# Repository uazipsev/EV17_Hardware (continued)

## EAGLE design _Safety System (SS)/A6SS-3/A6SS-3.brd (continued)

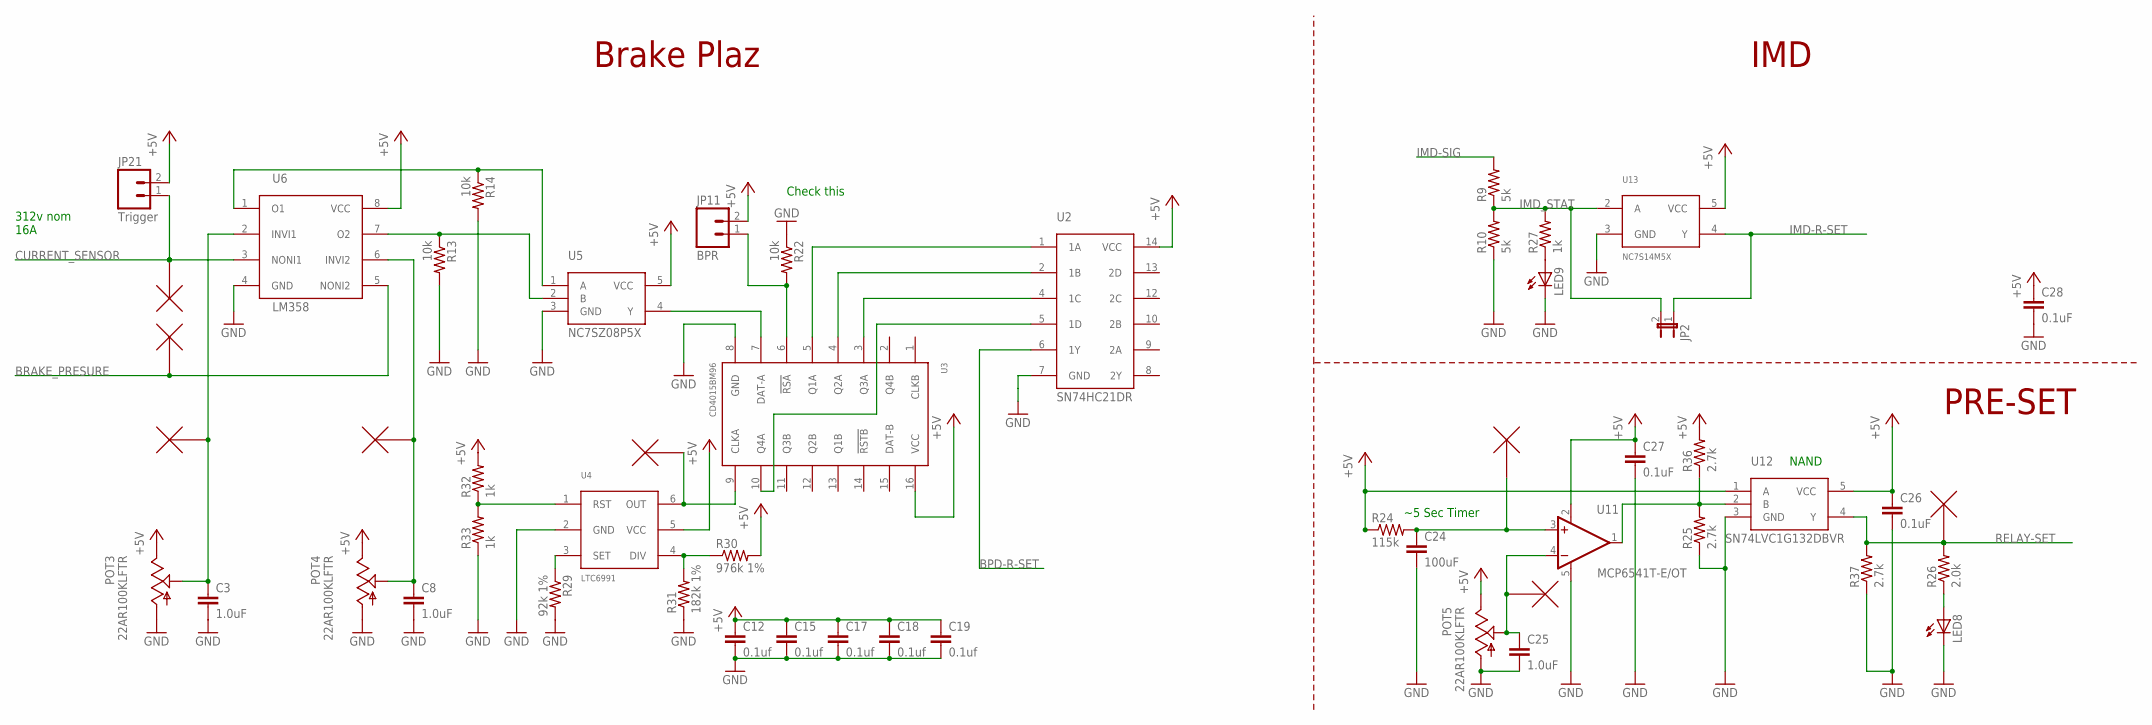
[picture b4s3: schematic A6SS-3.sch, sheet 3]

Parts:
BPR: TESTPOINT; R0603
C3, C8, C25: 1.0uF; 0805
C12, C15, C17, C18: 0.1uf; 0603-CAP
C19: 0.1uf; 0805
C24: 100uF; 1206
C26, C27: 0.1uF; 0603-CAP
C28: 0.1uF; 0805
CLK: TESTPOINT; R0603
CS: TESTPOINT; R0603
CST: TESTPOINT; R0603
JP2: JUMPER-2SMD-NO; SJ_2S-NO
JP11: BPR; MOLEX-1X2_LOCK
JP21: Trigger; MOLEX-1X2_LOCK
LED8, LED9: LEDCHIPLED_0603; CHIPLED_0603
PCG: TESTPOINT; R0603
POT3, POT4, POT5: 22AR100KLFTR
R9, R10: 5k; 0603-RES
R13, R14, R22: 10k; 0603-RES
R24: 115k; 1206
R25, R36, R37: 2.7k; 0603-RES
R26: 2.0k; 0603-RES
R27, R32, R33: 1k; 0603-RES
R29: 92k 1%; 0603-RES
R30: 976k 1%; 0603-RES
R31: 182k 1%; 0603-RES
RST: TESTPOINT; R0603
U2: SN74HC21DR; SO14
U3: CD4015BM96; SO-16
U4: LTC6991; TSOT-23-6
U5: NC7SZ08P5X; SOT23-5
U6: LM358; TSSOP-8
U11: MCP6541T-E/OT; SOT23-5
U12: SN74LVC1G132DBVR; SOT23-5
U13: NC7S14M5X; SOT23-5
U$2, U$3: TESTPOINT; R0603

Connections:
+5V: C12.1, C15.1, C17.1, C18.1, C19.1, C26.1, C27.1, C28.1, JP11.2, JP21.2, POT3.1 (CCW), POT4.1 (CCW), POT5.1 (CCW), R24.1, R30.2, R32.2, R36.2, U2.14 (VCC), U3.16 (VCC), U4.5 (VCC), U5.5 (VCC), U6.8 (VCC), U11.2 (V-), U12.1 (A), U12.5 (VCC), U13.5 (VCC); also elsewhere on the board
BPD-R-SET: U2.6 (1Y); also elsewhere on the board
BRAKE_PRESURE: BPR.1, BPR.2, U6.5 (NONI2); also elsewhere on the board
CURRENT_SENSOR: CS.1, CS.2, JP21.1, U6.3 (NONI1); also elsewhere on the board
GND: C3.2, C8.2, C12.2, C15.2, C17.2, C18.2, C19.2, C24.2, C25.2, C26.2, C27.2, C28.2, LED8.C, LED9.C, POT3.3 (CW), POT4.3 (CW), POT5.3 (CW), R10.1, R13.2, R14.2, R22.1, R25.1, R29.2, R31.1, R33.1, R37.1, U2.7 (GND), U3.8 (GND), U4.2 (GND), U5.3 (GND), U6.4 (GND), U11.5 (V+), U12.3 (GND), U13.3 (GND); also elsewhere on the board
IMD-R-SET: JP2.1, U13.4 (Y); also elsewhere on the board
IMD-SIG: R9.2; also elsewhere on the board
IMD_STAT: JP2.2, R9.1, R10.2, R27.2, U13.2 (A); also elsewhere on the board
unnamed: C25.1, POT5.2 (W), RST.1, RST.2, U11.4 (-IN)
unnamed: U2.5 (1D), U3.10 (Q4A)
unnamed: R30.1, R31.2, U4.4 (DIV)
unnamed: U3.7 (DAT-A), U5.4 (Y)
unnamed: JP11.1, R22.2, U3.6 (!RSA)
unnamed: C24.1, R24.2, U11.3 (+IN), U$2.1, U$2.2
unnamed: U2.1 (1A), U3.5 (Q1A)
unnamed: U2.2 (1B), U3.4 (Q2A)
unnamed: U2.4 (1C), U3.3 (Q3A)
unnamed: R29.1, U4.3 (SET)
unnamed: CLK.1, CLK.2, U3.9 (CLKA), U4.6 (OUT)
unnamed: C8.1, PCG.1, PCG.2, POT4.2 (W), U6.6 (INVI2)
unnamed: R25.2, R36.1, U11.1 (OUT), U12.2 (B)
unnamed: R32.1, R33.2, U4.1 (RST)
unnamed: C3.1, CST.1, CST.2, POT3.2 (W), U6.2 (INVI1)
unnamed: R14.1, U5.1 (A), U6.1 (O1)
unnamed: LED8.A, R26.1
unnamed: R13.1, U5.2 (B), U6.7 (O2)
unnamed: LED9.A, R27.1
RELAY-SET: R26.2, R37.2, U12.4 (Y), U$3.1, U$3.2; also elsewhere on the board

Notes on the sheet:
312v nom 16A
Check this
Brake Plaz
IMD
PRE-SET
~5 Sec Timer
NAND

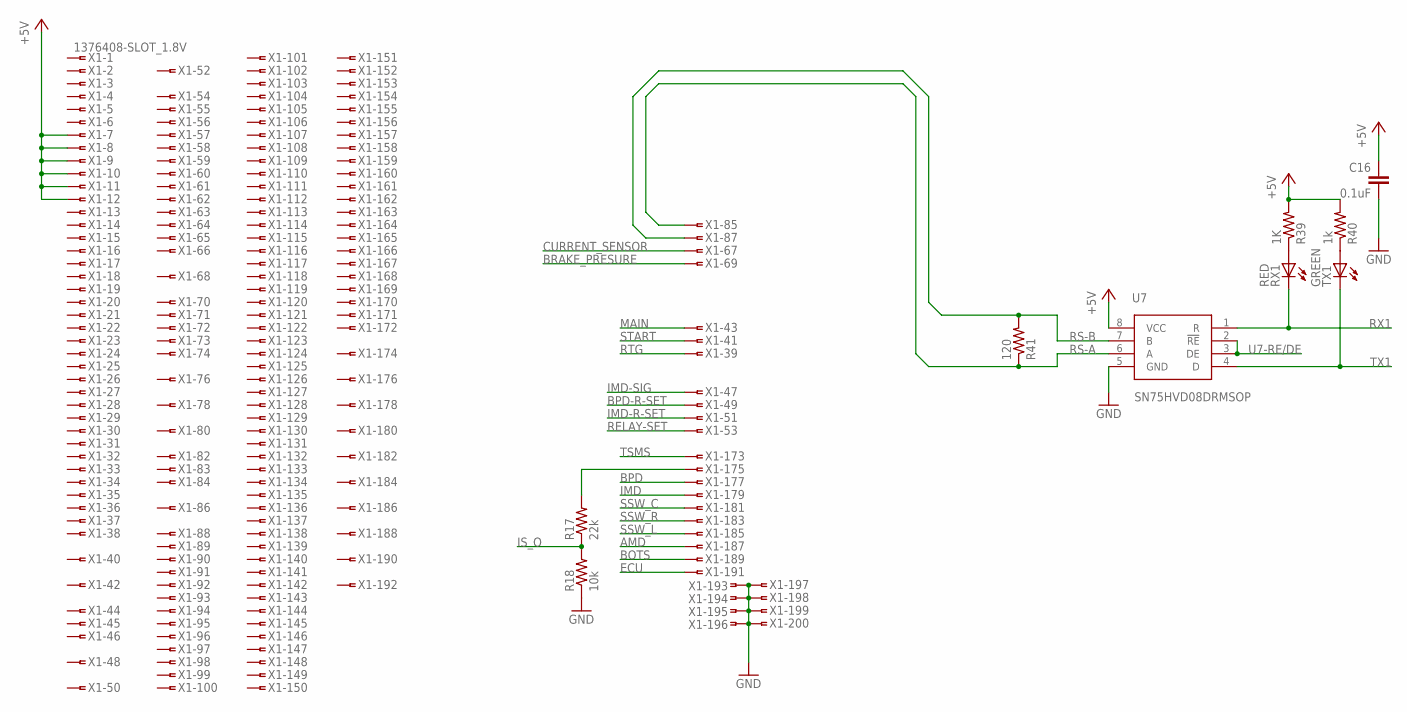
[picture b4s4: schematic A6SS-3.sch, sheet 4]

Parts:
C16: 0.1uF; 0603-CAP
R17: 22k; 0805
R18: 10k; 0805
R39: 1K; R0603
R40: 1k; R0603
R41: 120; R0603
RX1: RED; CHIPLED_0603
TX1: GREEN; CHIPLED_0603
U7: SN75HVD08DRMSOP; MSOP-8
X1: 1376408-SLOT_1.8V; SLOT-1376408-1_1.8V

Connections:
+5V: C16.1, R39.2, R40.2, U7.8 (VCC), X1.7, X1.8, X1.9, X1.10, X1.11, X1.12; also elsewhere on the board
AMD: X1.187; also elsewhere on the board
BOTS: X1.189; also elsewhere on the board
BPD: X1.177; also elsewhere on the board
BPD-R-SET: X1.49; also elsewhere on the board
BRAKE_PRESURE: X1.69; also elsewhere on the board
CURRENT_SENSOR: X1.67; also elsewhere on the board
ECU: X1.191; also elsewhere on the board
GND: C16.2, R18.1, U7.5 (GND), X1.193, X1.194, X1.195, X1.196, X1.197, X1.198, X1.199, X1.200; also elsewhere on the board
IMD: X1.179; also elsewhere on the board
IMD-R-SET: X1.51; also elsewhere on the board
IMD-SIG: X1.47; also elsewhere on the board
IS_O: R17.1, R18.2; also elsewhere on the board
MAIN: X1.43; also elsewhere on the board
unnamed: R17.2, X1.175
unnamed: R40.1, TX1.A
unnamed: R39.1, RX1.A
RELAY-SET: X1.53; also elsewhere on the board
RS-A: R41.1, U7.6 (A), X1.85
RS-B: R41.2, U7.7 (B), X1.87
RTG: X1.39; also elsewhere on the board
RX1: RX1.C, U7.1 (R); also elsewhere on the board
SSW_C: X1.181; also elsewhere on the board
SSW_L: X1.185; also elsewhere on the board
SSW_R: X1.183; also elsewhere on the board
START: X1.41; also elsewhere on the board
TSMS: X1.173; also elsewhere on the board
TX1: TX1.C, U7.4 (D); also elsewhere on the board
U7-RE/DE: U7.2 (!RE), U7.3 (DE); also elsewhere on the board

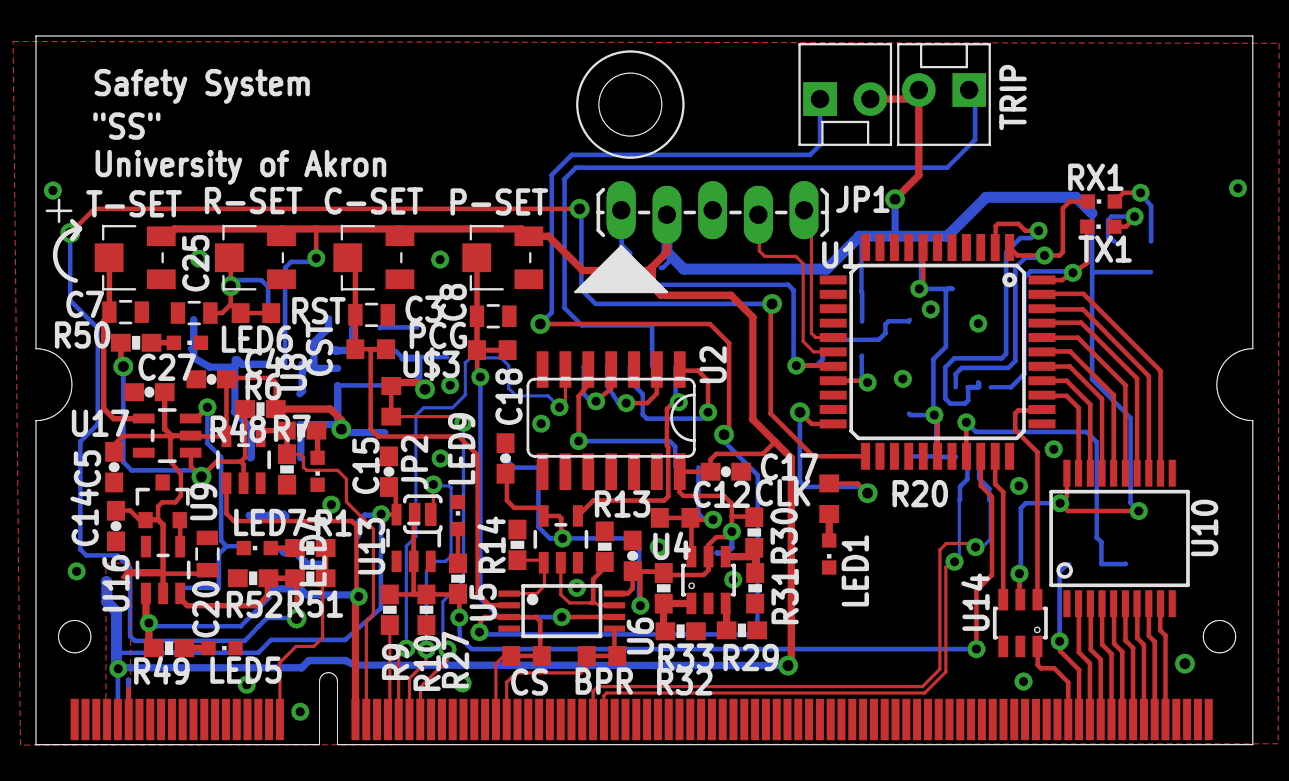
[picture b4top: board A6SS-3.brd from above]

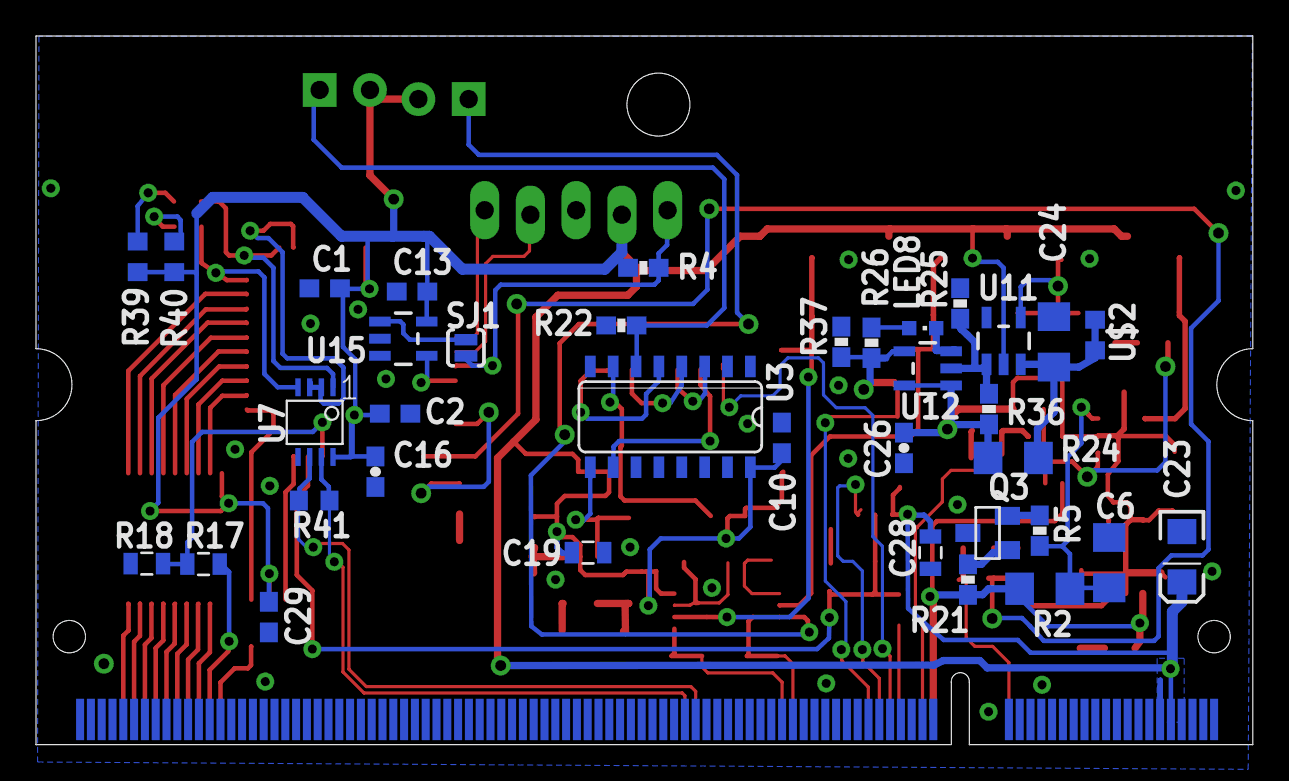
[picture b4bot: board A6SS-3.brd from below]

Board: 2 copper layers, 67.6 x 39.4 mm, 105 parts (36 on the bottom side), 77 nets.

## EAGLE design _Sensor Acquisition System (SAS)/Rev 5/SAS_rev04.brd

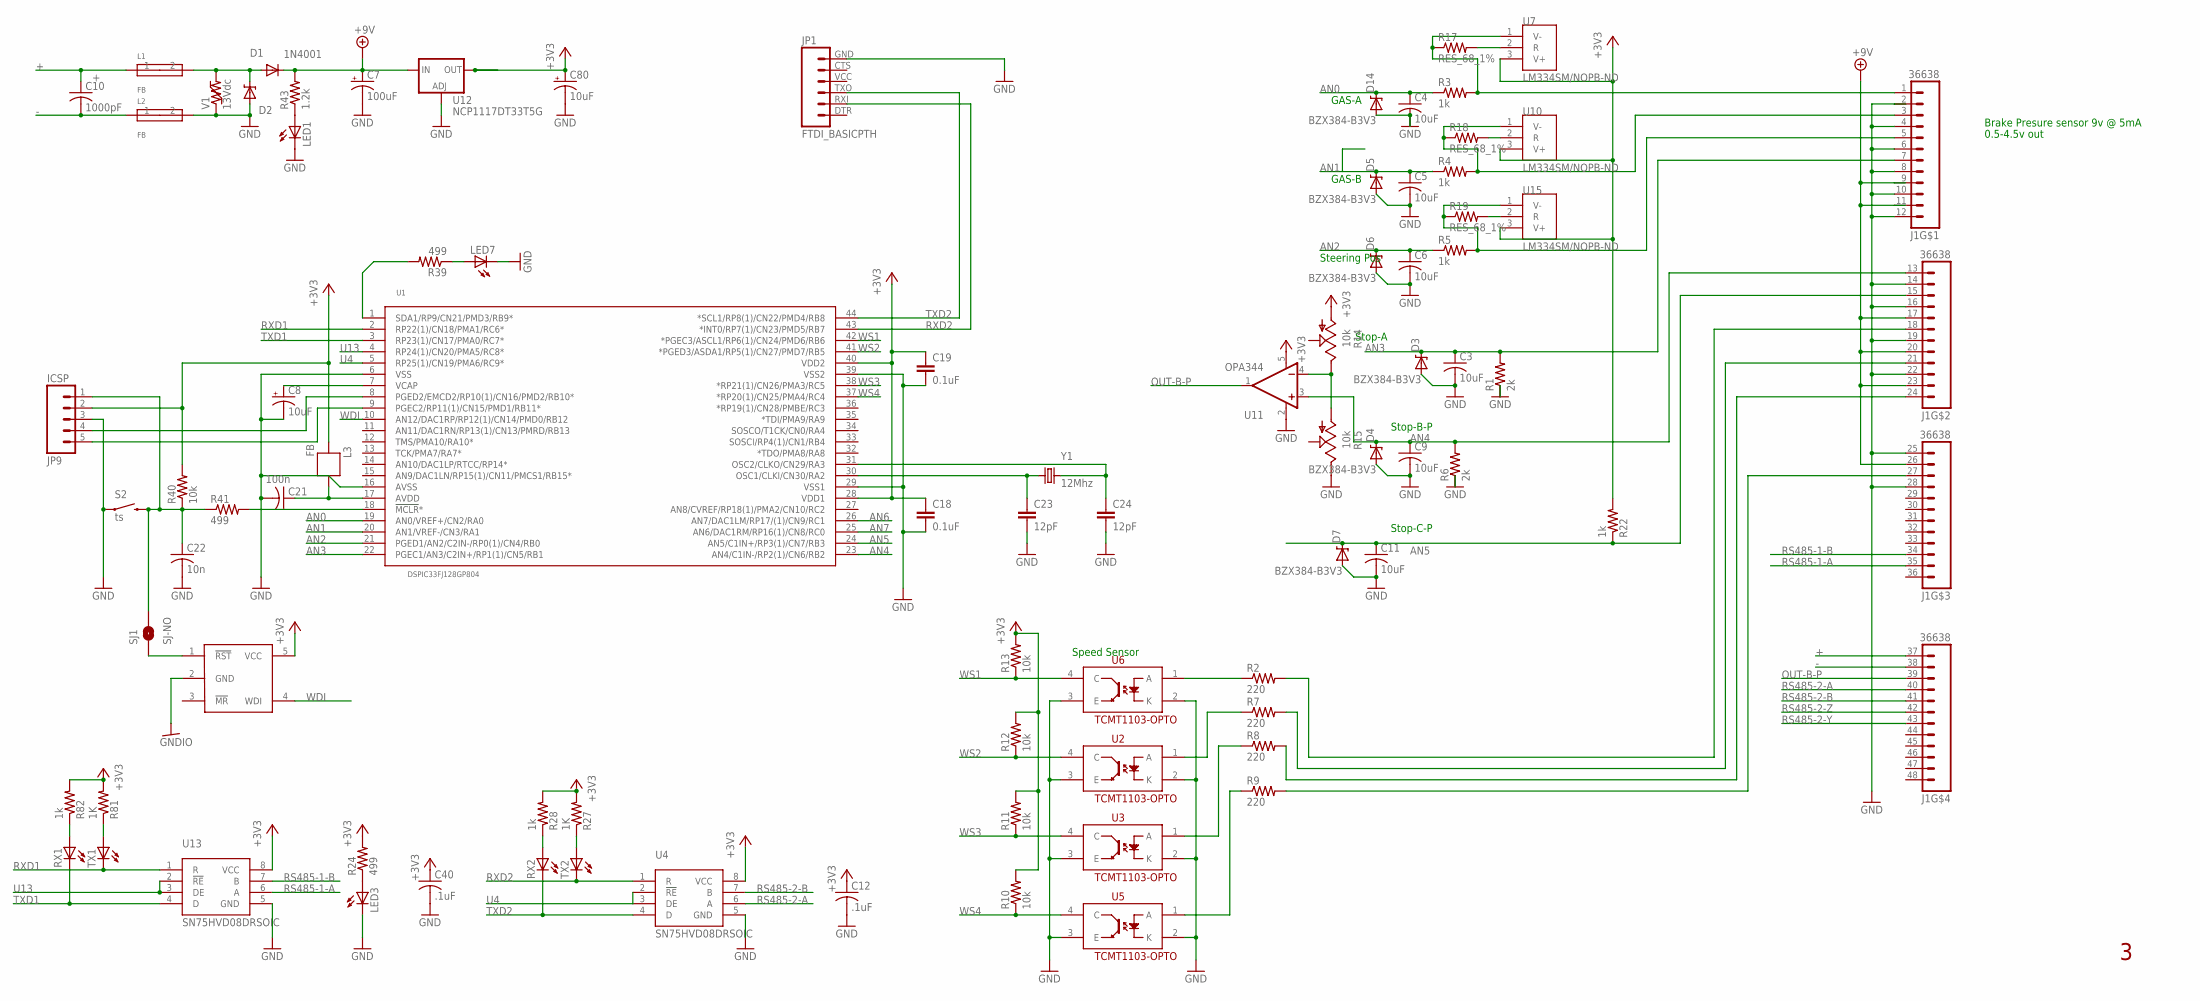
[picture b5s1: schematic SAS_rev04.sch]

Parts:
C3, C4, C5, C6, C9, C11: 10uF; C0805
C7: 100uF; EIA7343
C8: 10uF; EIA3216-16V
C10: 1000pF; C1825
C12, C40: .1uF; 0603
C18, C19: 0.1uF; 0805
C21: 100n; C0805
C22: 10n; 0603
C23, C24: 12pF; 0805
C80: 10uF; POLC1206
D1: 1N4001; SOD123
D2: MM5Z30; SOD-523F
D3, D4, D5, D6, D7, D14: BZX384-B3V3; SOD-323
J1: 36638
JP1: FTDI_BASICPTH; FTDI_BASIC
JP9: ICSP; 1X05_LOCK_LONGPADS
L1, L2, L3: FB; 0603
LED1, LED3, LED7: LEDCHIP-LED0805; CHIP-LED0805
R1, R6: 2k; 0805
R2, R7, R8, R9: 220; 0603
R3, R4, R5, R82: 1k; 0603
R10, R11, R12, R13: 10k; 0603
R14, R15: 10k; PVG3
R17, R18, R19: RES_68_1%; 0603
R22, R28: 1k; 0805
R24, R39: 499; 0603
R27: 1K; 0805
R40: 10k; 0805
R41: 499; 0805
R43: 1.2k; 0805
R81: 1K; 0603
RX1, RX2: LEDCHIPLED_0805; CHIPLED_0805
S2: ts; TACTILE-PTH
SJ1: SJ-NO; SJ_2S-NO
TX1, TX2: LEDCHIPLED_0805; CHIPLED_0805
U1: DSPIC33FJ128GP804; TQFP-44
U2, U3, U5, U6: TCMT1103-OPTO; SSOP-4
U4, U13: SN75HVD08DRSOIC; SO-8
U7, U10, U15: LM334SM/NOPB-ND; SO-8
U9: MAX823; SOT23-5L
U11: OPA344; SOT23-5
U12: NCP1117DT33T5G; V-REG_DPACK
V1: 13Vdc; 0603
Y1: 12Mhz; CRYSTAL-SMD-5X3

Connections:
+: C10.1, J1.37 (1), L1.1
+3V3: C12.1 (+), C18.1, C19.1, C40.1 (+), C80.1 (+), JP9.2, L3.2, R10.2, R11.2, R12.2, R13.2, R14.1 (CW), R22.2, R24.2, R27.2, R28.2, R40.2, R81.2, R82.2, U1.28 (VDD1), U1.40 (VDD2), U4.8 (VCC), U7.3 (V+), U9.5 (VCC), U10.3 (V+), U11.5 (V+), U12.4 (OUT), U13.8 (VCC), U15.3 (V+)
+9V: C7.A (+), D1.C, J1.9, J1.11, J1.17 (5), J1.20 (8), J1.23 (11), J1.26 (2), R43.2, U12.3 (IN)
-: C10.2, J1.38 (2), L2.1
AN0: C4.1, D14.1 (C), R3.1, U1.19 (AN0/VREF+/CN2/RA0)
AN1: C5.1, D5.1 (C), R4.1, U1.20 (AN1/VREF-/CN3/RA1)
AN2: C6.1, D6.1 (C), R5.1, U1.21 (PGED1/AN2/C2IN-/RP0(1)/CN4/RB0)
AN3: C3.1, D3.1 (C), J1.7, R1.2, U1.22 (PGEC1/AN3/C2IN+/RP1(1)/CN5/RB1)
AN4: C9.1, D4.1 (C), J1.13 (1), R6.2, U1.23 (AN4/C1IN-/RP2(1)/CN6/RB2), U11.3 (+IN)
AN5: C11.1, D7.1 (C), J1.15 (3), R22.1, U1.24 (AN5/C1IN+/RP3(1)/CN7/RB3)
AN6: U1.26 (AN7/DAC1LM/RP17/(1)/CN9/RC1)
AN7: U1.25 (AN6/DAC1RM/RP16(1)/CN8/RC0)
GHT: D1.A, D2.C, L1.2, V1.2
GND: C3.2, C4.2, C5.2, C6.2, C7.C (-), C8.C (-), C9.2, C11.2, C12.2 (-), C18.2, C19.2, C21.2, C22.2 (-), C23.2, C24.2, C40.2 (-), C80.2 (-), D2.A, D3.2 (A), D4.2 (A), D5.2 (A), D6.2 (A), D7.2 (A), D14.2 (A), J1.2, J1.4, J1.6, J1.8, J1.10, J1.12, J1.14 (2), J1.16 (4), J1.19 (7), J1.22 (10), J1.25 (1), J1.28 (4), JP1.GND (6), JP9.3, L2.2, LED1.C, LED3.C, LED7.C, R1.1, R6.1, R15.3 (CCW), S2.1, U1.6 (VSS), U1.16 (AVSS), U1.29 (VSS1), U1.39 (VSS2), U2.2 (K), U2.3 (E), U3.2 (K), U3.3 (E), U4.5 (GND), U5.2 (K), U5.3 (E), U6.2 (K), U6.3 (E), U11.2 (V-), U12.1 (ADJ), U13.5 (GND), V1.1
GNDIO: U9.2 (GND)
unnamed: C22.1 (+), JP9.1, R40.1, R41.1, S2.3 (2), SJ1.2
unnamed: C21.1, L3.1, U1.17 (AVDD)
unnamed: J1.1, R3.2, R17.1, U7.1 (V-)
unnamed: C8.A (+), U1.7 (VCAP)
unnamed: R39.2, U1.1 (SDA1/RP9/CN21/PMD3/RB9*)
unnamed: LED1.A, R43.1
unnamed: R17.2, U7.2 (R)
unnamed: R41.2, U1.18 (!MCLR!*)
unnamed: R14.3 (CCW), R15.1 (CW), U11.4 (-IN)
unnamed: SJ1.1, U9.1 (!RST)
unnamed: J1.18 (6), R2.2
unnamed: JP9.4, U1.8 (PGED2/EMCD2/RP10(1)/CN16/PMD2/RB10*)
unnamed: JP9.5, U1.9 (PGEC2/RP11(1)/CN15/PMD1/RB11*)
unnamed: J1.21 (9), R7.2
unnamed: J1.24 (12), R8.2
unnamed: J1.27 (3), R9.2
unnamed: R2.1, U6.1 (A)
unnamed: R7.1, U2.1 (A)
unnamed: R8.1, U3.1 (A)
unnamed: R9.1, U5.1 (A)
unnamed: R18.2, U10.2 (R)
unnamed: LED3.A, R24.1
unnamed: J1.3, R4.2, R18.1, U10.1 (V-)
unnamed: J1.5, R5.2, R19.1, U15.1 (V-)
unnamed: R27.1, TX2.A
unnamed: R28.1, RX2.A
unnamed: R19.2, U15.2 (R)
unnamed: LED7.A, R39.1
unnamed: C24.1, U1.31 (OSC2/CLKO/CN29/RA3), Y1.3 (2)
unnamed: C23.1, U1.30 (OSC1/CLKI/CN30/RA2), Y1.1
unnamed: R81.1, TX1.A
unnamed: R82.1, RX1.A
OUT-B-P: J1.39 (3), U11.1 (OUT)
RS485-1-A: J1.35 (11), U13.6 (A)
RS485-1-B: J1.34 (10), U13.7 (B)
RS485-2-A: J1.40 (4), U4.6 (A)
RS485-2-B: J1.41 (5), U4.7 (B)
RS485-2-Y: J1.43 (7)
RS485-2-Z: J1.42 (6)
RXD1: TX1.C, U1.2 (RP22(1)/CN18/PMA1/RC6*), U13.1 (R)
RXD2: JP1.RXI (2), TX2.C, U1.43 (*INT0/RP7(1)/CN23/PMD5/RB7), U4.1 (R)
TXD1: RX1.C, U1.3 (RP23(1)/CN17/PMA0/RC7*), U13.4 (D)
TXD2: JP1.TXO (3), RX2.C, U1.44 (*SCL1/RP8(1)/CN22/PMD4/RB8), U4.4 (D)
U4: U1.5 (RP25(1)/CN19/PMA6/RC9*), U4.2 (!RE), U4.3 (DE)
U13: U1.4 (RP24(1)/CN20/PMA5/RC8*), U13.2 (!RE), U13.3 (DE)
WDI: U1.10 (AN12/DAC1RP/RP12(1)/CN14/PMD0/RB12), U9.4 (WDI)
WS1: R13.1, U1.42 (*PGEC3/ASCL1/RP6(1)/CN24/PMD6/RB6), U6.4 (C)
WS2: R12.1, U1.41 (*PGED3/ASDA1/RP5(1)/CN27/PMD7/RB5), U2.4 (C)
WS3: R11.1, U1.38 (*RP21(1)/CN26/PMA3/RC5), U3.4 (C)
WS4: R10.1, U1.37 (*RP20(1)/CN25/PMA4/RC4), U5.4 (C)

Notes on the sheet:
GAS-A
GAS-B
Steering Pos
Stop-A
Stop-B-P
Stop-C-P
Speed Sensor
Brake Presure sensor 9v @ 5mA
0.5-4.5v out

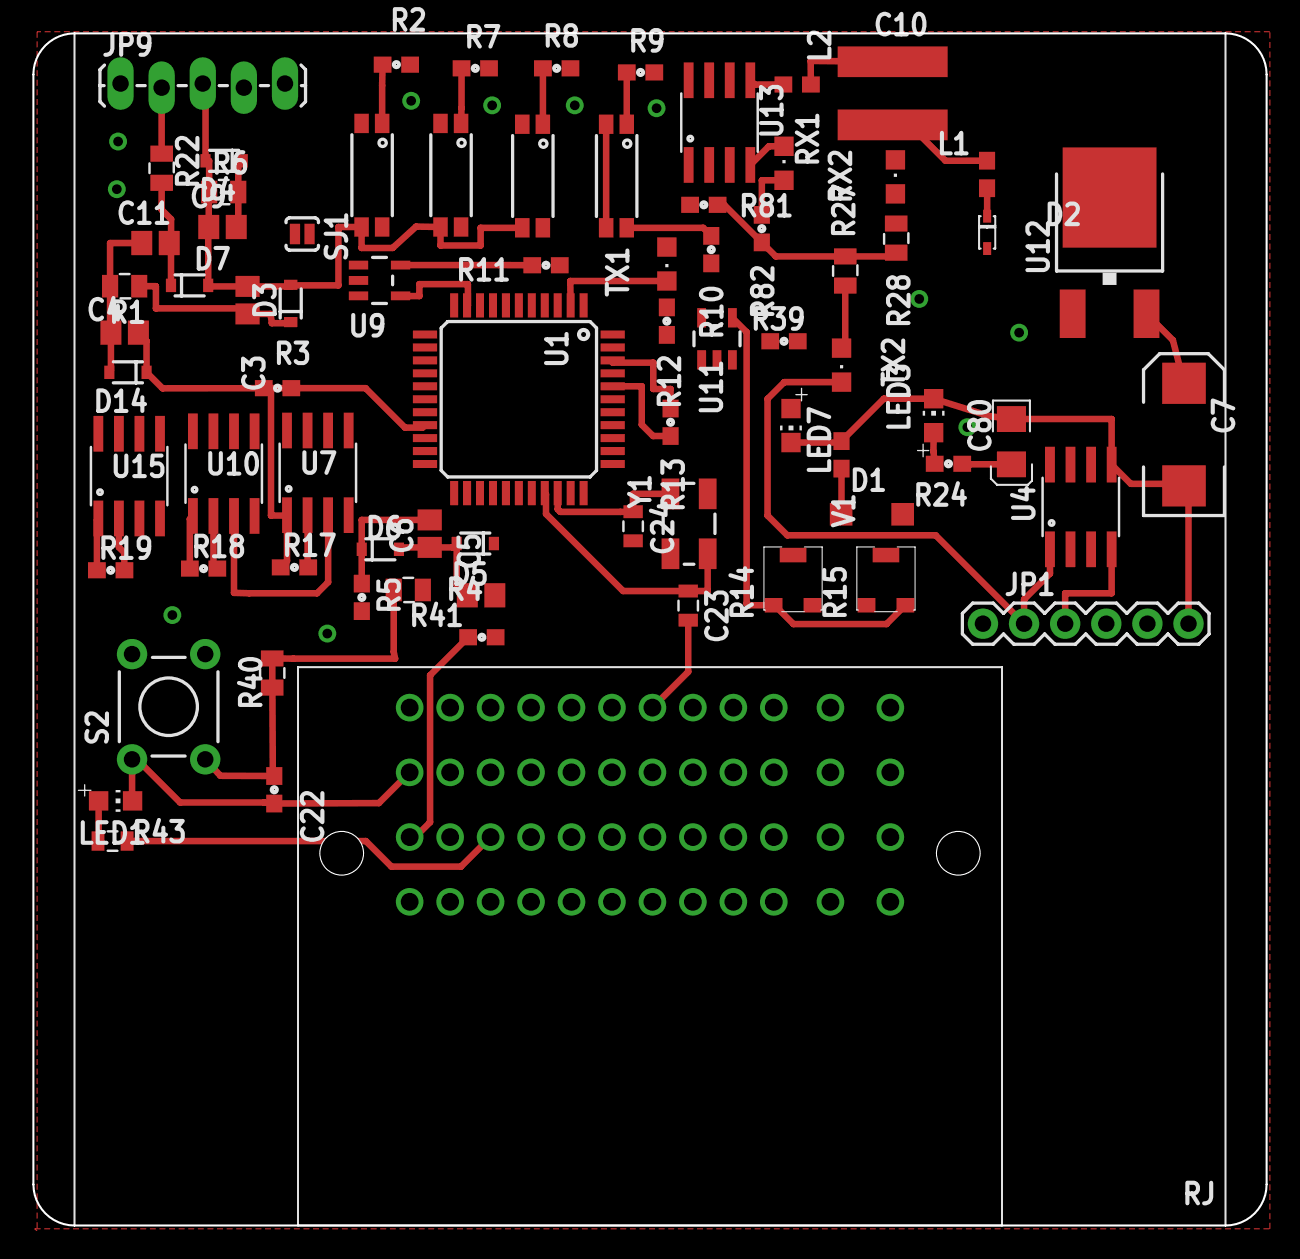
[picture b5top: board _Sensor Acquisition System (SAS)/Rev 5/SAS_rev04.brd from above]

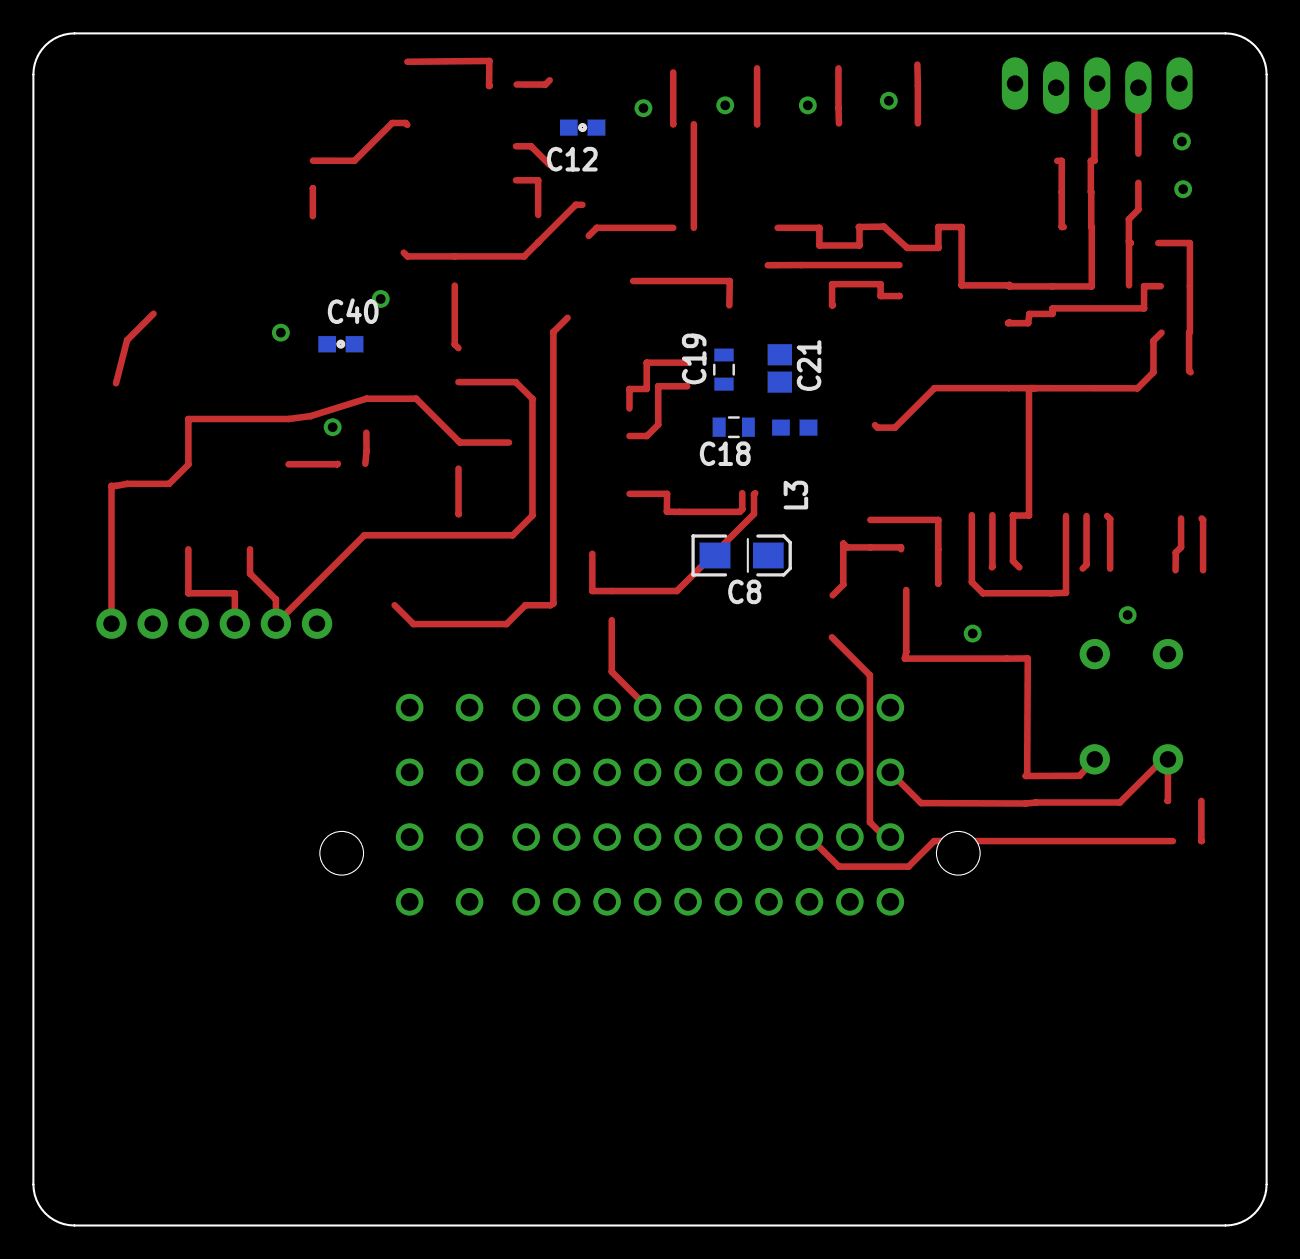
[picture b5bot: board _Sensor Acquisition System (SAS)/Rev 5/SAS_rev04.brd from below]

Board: 2 copper layers, 76.2 x 73.7 mm, 85 parts (7 on the bottom side), 60 nets.

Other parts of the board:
U$2: L-L

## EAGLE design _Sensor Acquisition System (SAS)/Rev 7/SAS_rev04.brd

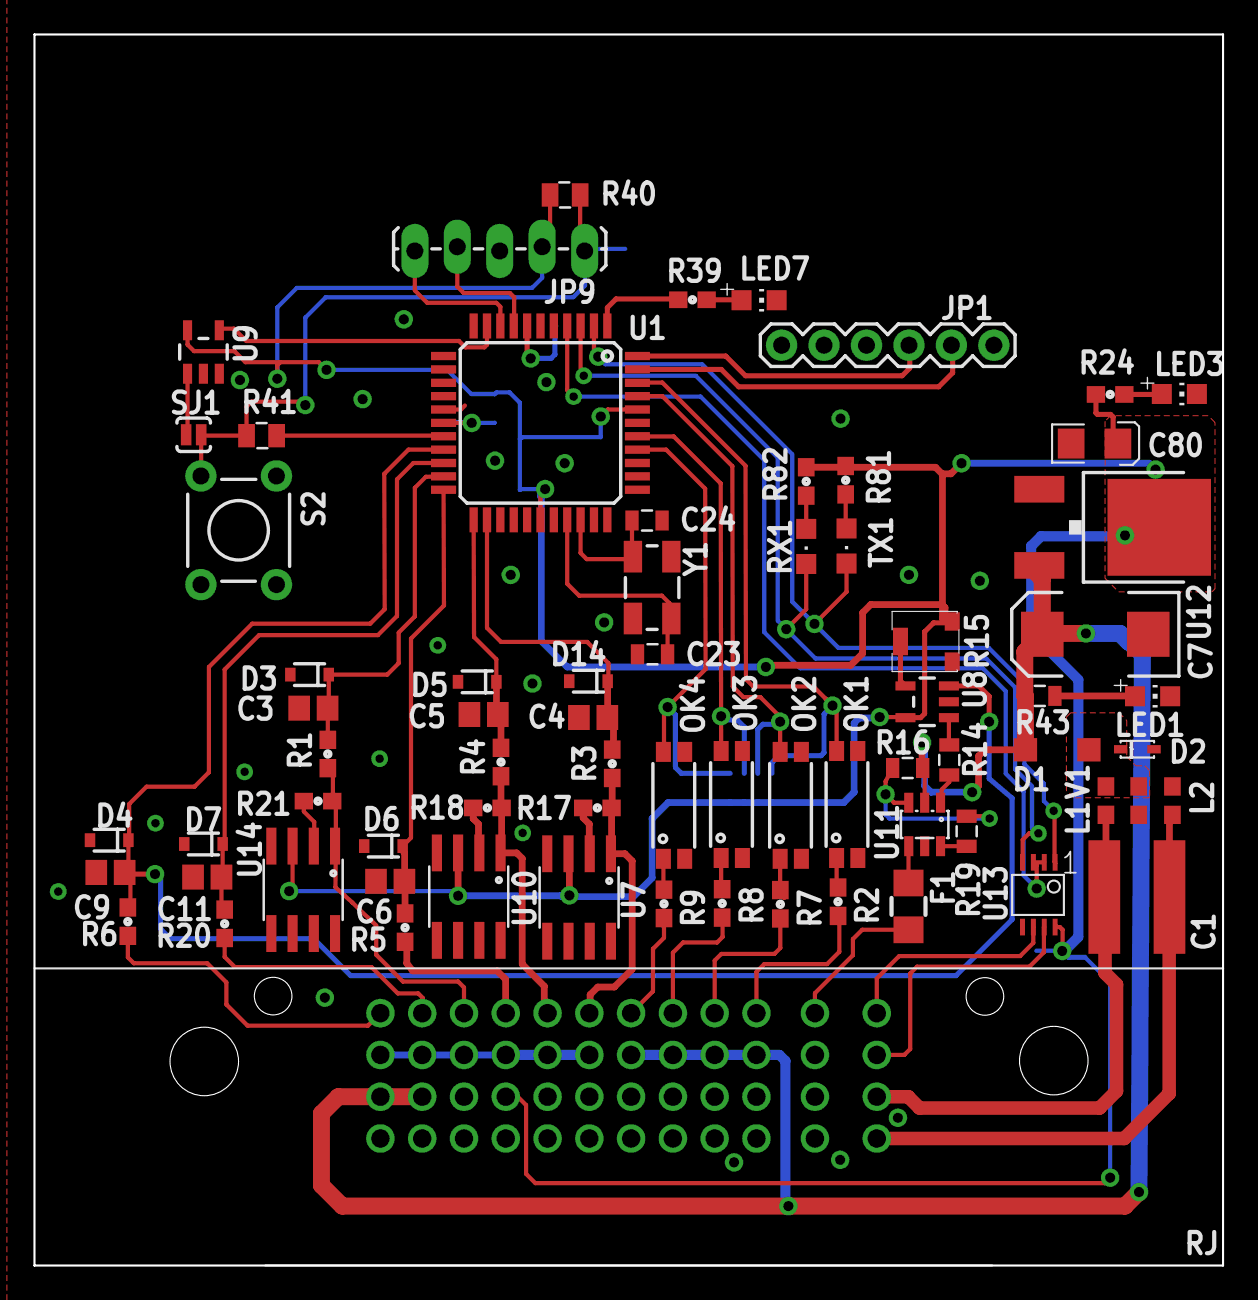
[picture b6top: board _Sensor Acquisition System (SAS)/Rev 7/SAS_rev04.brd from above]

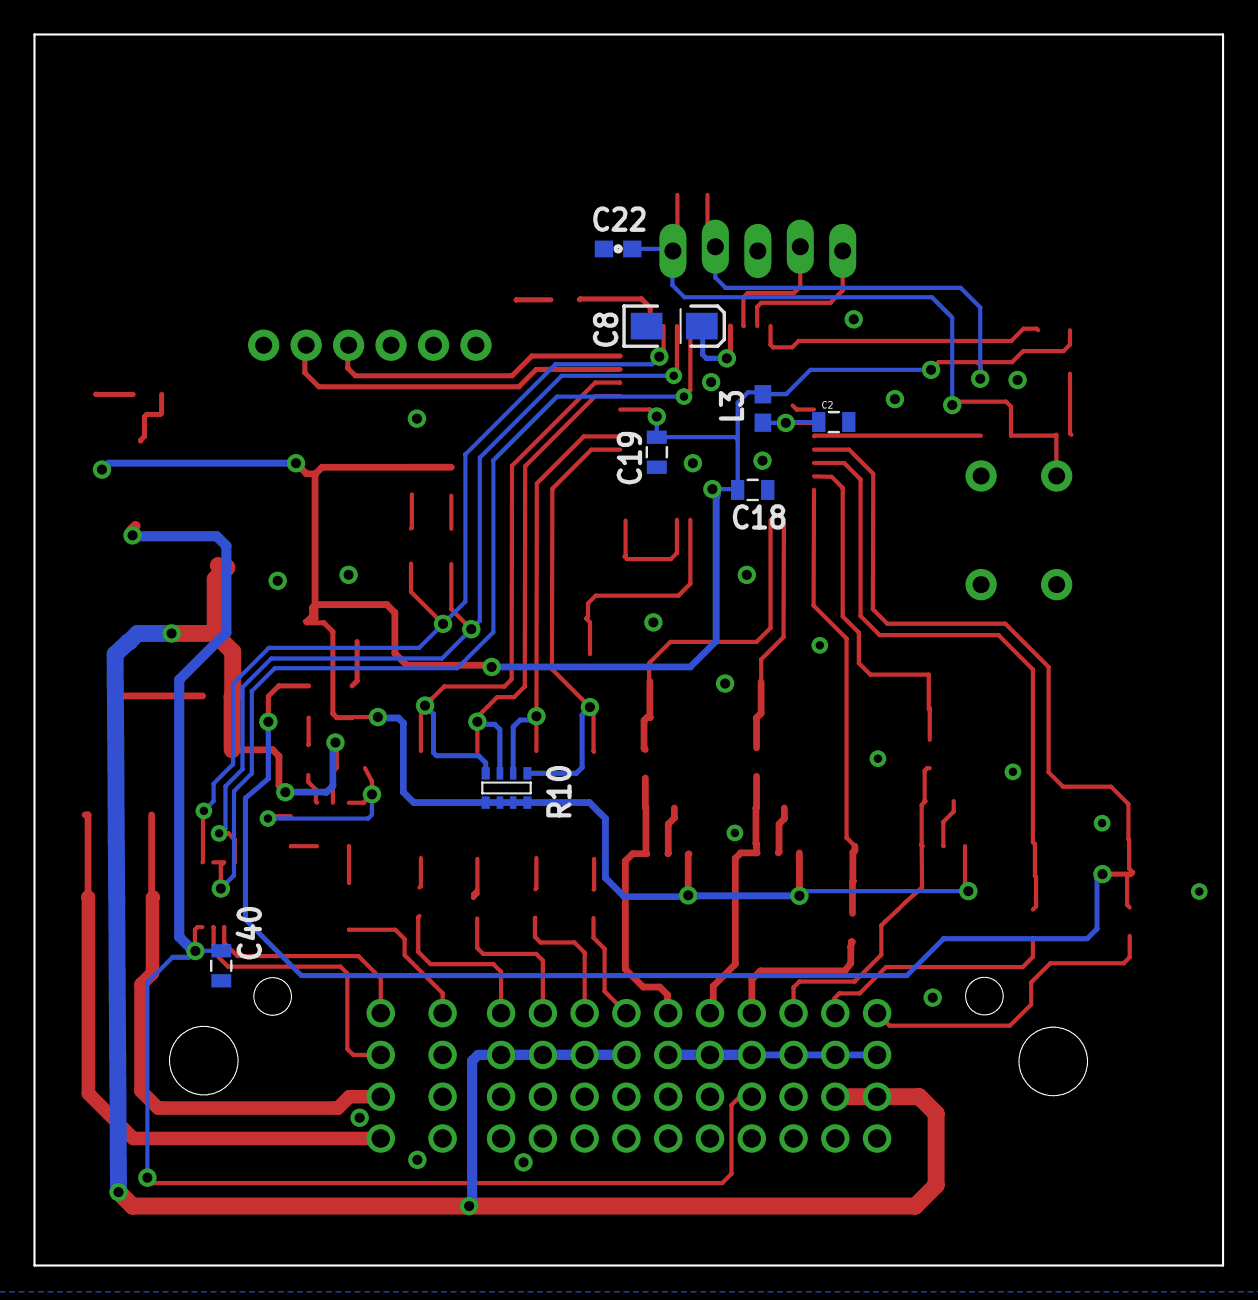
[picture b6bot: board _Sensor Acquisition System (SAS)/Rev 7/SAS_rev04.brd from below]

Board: 2 copper layers, 71.1 x 73.7 mm, 80 parts (8 on the bottom side), 63 nets.

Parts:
C1: CAP_1000PF_2KV; C1825
C2, C40: .1uF; 0805
C3, C4, C5, C6, C9, C11: 10uF; C0805
C7: 100uF; EIA7343
C8: 10uF; EIA3216-16V
C18, C19: 0.1uF; 0805
C22: 10n; 0603
C23, C24: 12pF; 0805
C80: 10uF; POLC1206
D1: 1N4001; SOD123
D2: MM5Z30; SOD-523F
D3, D4, D5, D6, D7, D14: BZX384-B3V3; SOD-323
F1: 120mA; 1206
J1: 36638NEW; 36638-M
JP1: FTDI_BASICPTH; FTDI_BASIC
JP9: ICSP; 1X05_LOCK_LONGPADS
L1, L2, L3: FB; 0603
LED1, LED3, LED7: CHIP-LED0805
OK1, OK2, OK3, OK4: TCMT1103; SOP-4
R1, R3, R4, R5, R6, R20, R82: 1k; 0603
R2, R7, R8, R9: 220; 0603
R10: 10K; MNR14
R14: 1K; 0805
R15: 10k; PVG3
R16, R19: 10K; 0805
R17, R18, R21: 68; 0603
R24, R39: 499; 0603
R40: 10k; 0805
R41: 499; 0805
R43: 1.2k; 0805
R81: 1K; 0603
RX1: CHIPLED_0805
S2: ts; TACTILE-PTH
SJ1: SJ-NO; SJ_2S-NO
TX1: CHIPLED_0805
U1: DSPIC33FJ128GP804; TQFP-44
U7, U10, U14: LM334SM/NOPB-ND; SO-8
U8: OPA344; SOT23-5
U9: MAX823; SOT23-5L
U11: DMG6602SVTQ; SOT23-6
U12: NCP1117DT33T5G; V-REG_DPACK
U13: SN75HVD08DRMSOP; MSOP-8
U$1: LOGO16-L; 2016-LOGO-L
V1: 13Vdc; 0603
Y1: 12Mhz; CRYSTAL-SMD-5X3

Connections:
+: C1.1, J1.47, L1.1
+3V3: C18.1, C19.1, C40.1, C80.1, J1.15, JP9.2, L3.2, R10.5, R10.6, R10.7, R10.8, R15.1, R24.2, R40.2, R81.2, R82.2, U1.28, U1.40, U7.3, U8.5, U9.5, U10.3, U12.4, U13.8, U14.3
+9V: C7.A, D1.C, J1.3, J1.7, J1.26, J1.30, J1.34, J1.38, R16.1, R43.2, U11.2, U12.3
-: C1.2, J1.48, L2.1
AN0: C9.1, D4.1, R6.1, U1.19, U8.3
AN1: C11.1, D7.1, R20.1, U1.20
AN2: C3.1, D3.1, R1.1, U1.21
AN3: C6.1, D6.1, R5.1, U1.22
AN4: C5.1, D5.1, R4.1, U1.23
AN5: C4.1, D14.1, R3.1, U1.24
GHT: D1.A, D2.C, L1.2, V1.2
GND: C2.2, C3.2, C4.2, C5.2, C6.2, C7.C, C8.C, C9.2, C11.2, C18.2, C19.2, C22.2, C23.2, C24.2, C40.2, C80.2, D2.A, D3.2, D4.2, D5.2, D6.2, D7.2, D14.2, J1.2, J1.4, J1.6, J1.8, J1.10, J1.12, J1.14, J1.18, J1.22, J1.27, J1.31, J1.35, J1.39, JP1.GND, JP9.3, L2.2, LED1.C, LED3.C, LED7.C, OK1.2, OK1.3, OK2.2, OK2.3, OK3.2, OK3.3, OK4.2, OK4.3, R15.3, S2.1, U1.6, U1.16, U1.29, U1.39, U8.2, U11.5, U12.1, U13.5, V1.1
unnamed: C22.1, JP9.1, R40.1, R41.1, S2.3, SJ1.2
unnamed: C2.1, L3.1, U1.17
unnamed: J1.21, R3.2, R17.1, U7.1
unnamed: C8.A, U1.7
unnamed: R39.2, U1.1
unnamed: LED1.A, R43.1
unnamed: R17.2, U7.2
unnamed: R41.2, U1.18
unnamed: R15.2, U8.4
unnamed: SJ1.1, U9.1
unnamed: J1.37, R2.2
unnamed: JP9.4, U1.8
unnamed: JP9.5, U1.9
unnamed: J1.33, R7.2
unnamed: J1.29, R8.2
unnamed: J1.25, R9.2
unnamed: OK1.1, R2.1
unnamed: OK2.1, R7.1
unnamed: OK3.1, R8.1
unnamed: OK4.1, R9.1
unnamed: R18.2, U10.2
unnamed: LED3.A, R24.1
unnamed: J1.17, R4.2, R18.1, U10.1
unnamed: J1.9, R1.2, R21.1, U14.1
unnamed: J1.13, R5.2
unnamed: J1.5, R20.2
unnamed: R14.2, U8.1
unnamed: LED7.A, R39.1
unnamed: C24.1, U1.31, Y1.3
unnamed: C23.1, U1.30, Y1.1
unnamed: R19.2, U11.6
unnamed: R16.2, R19.1, U11.3
unnamed: F1.1, U11.4
unnamed: J1.1, R6.2
unnamed: R21.2, U14.2
unnamed: R81.1, TX1.A
unnamed: R82.1, RX1.A
OUT-B_P: F1.2, J1.41
RS485-1-A: J1.45, U13.6
RS485-1-B: J1.46, U13.7
RXD1: TX1.C, U1.2, U13.1
RXD2: JP1.RXI, U1.43
TXD1: RX1.C, U1.3, U13.4
TXD2: JP1.TXO, U1.44
U13: U1.4, U13.2, U13.3
WDI: U1.10, U9.4
WS1: OK1.4, R10.4, U1.42
WS2: OK2.4, R10.3, U1.41
WS3: OK3.4, R10.2, U1.38
WS4: OK4.4, R10.1, U1.37
YO: R14.1, U11.1
